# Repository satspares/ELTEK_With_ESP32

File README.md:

ELTEK Flatpack2 control using ESP32/c3 DWIN Display DMG48320C035_03WTC (480x320) or any DWIN TTL 800x480 display eg. DMG80480C043_01WTC.

18th September 2025 added config for DWIN Display DMG48270C043_04WTC 480x272 (change link on display to ttl).

Added Eltek network ID change to new menu item.

In the can-bus-kicad directory is a PCB design using ESP32c3 but you can use any ESP32 (5v supply needed) and a sn65hvd230 CAN Chip.

I am still working on the code for the older Flatpack2's so the code is not complete yet (fine for V3 Elteks)

The displays are from the DWIN Store on Aliexpress about 18.00usd plus carriage DMG48270C043_04WTC recommended.

As the Eltex was designed to charge batteries the current limit when active reduces the output voltage to approx. 47volts.
When this happens we display a warning and sound a beep also put a ESP32 output pin high. (pull a relay etc. with a driver transistor)

The folder to upload to the display via. sdcard is DWIN_SET
Its also worth looking at the DWIN docs. in my github https://github.com/satspares/DWIN_DGUS_HMI

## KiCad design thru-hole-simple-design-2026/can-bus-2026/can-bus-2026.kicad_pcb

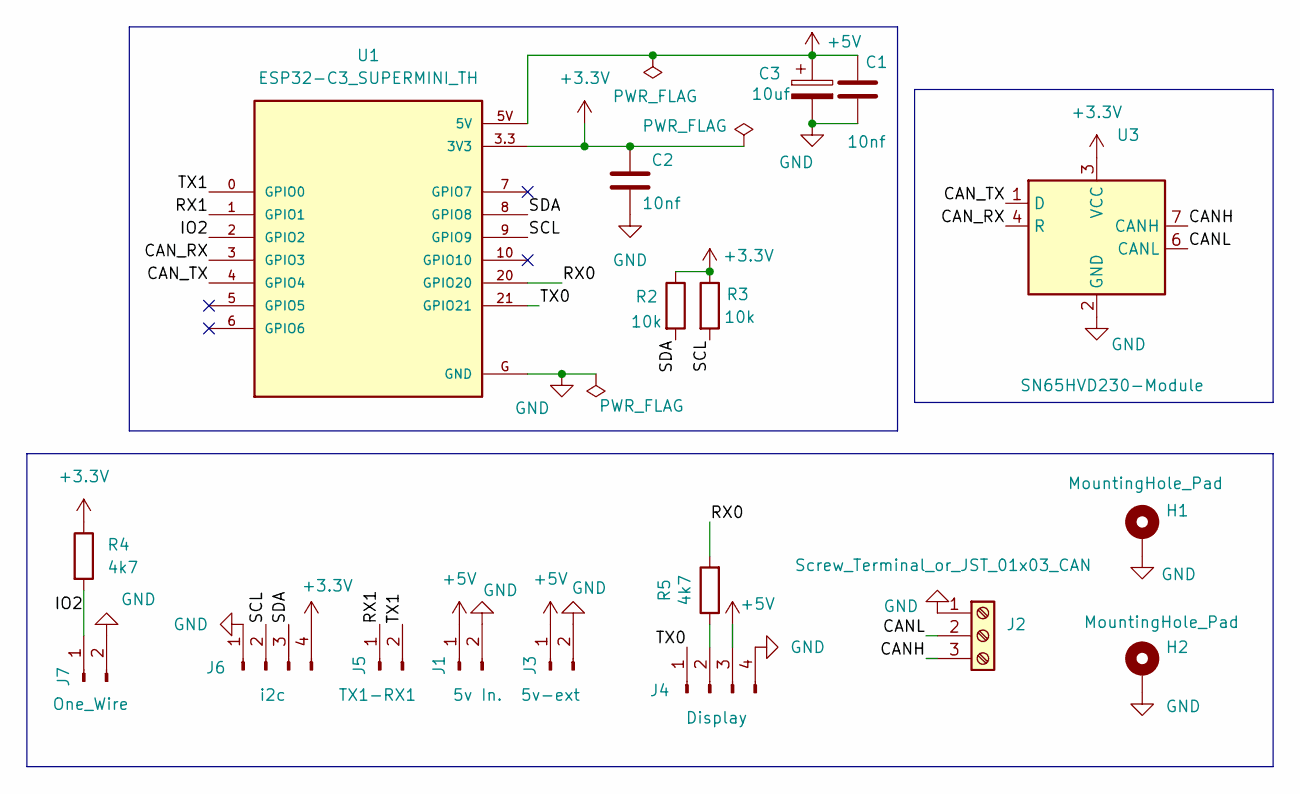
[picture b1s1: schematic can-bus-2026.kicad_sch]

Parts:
C1, C2: 10nf; C_Disc_D3.4mm_W2.1mm_P2.50mm
C3: 10uf; CP_Radial_D5.0mm_P2.50mm
H1, H2: MountingHole_Pad; MountingHole_3.5mm_Pad_Via
J1: 5v In.; JST_EH_B2B-EH-A_1x02_P2.50mm_Vertical
J2: Screw_Terminal_or_JST_01x03_CAN; TerminalBlock_Xinya_XY308-2.54-3P_1x03_P2.54mm_Horizontal
J3: 5v-ext; JST_EH_B2B-EH-A_1x02_P2.50mm_Vertical
J4: Display; JST_EH_B4B-EH-A_1x04_P2.50mm_Vertical
J5: TX1-RX1; JST_EH_B2B-EH-A_1x02_P2.50mm_Vertical
J6: i2c; JST_EH_B4B-EH-A_1x04_P2.50mm_Vertical
J7: One_Wire; JST_EH_B2B-EH-A_1x02_P2.50mm_Vertical
R2, R3: 10k; R_Axial_DIN0207_L6.3mm_D2.5mm_P7.62mm_Horizontal
R4, R5: 4k7; R_Axial_DIN0207_L6.3mm_D2.5mm_P7.62mm_Horizontal
U1: ESP32-C3_SUPERMINI_TH; MODULE_ESP32-C3_SUPERMINI
U3: SN65HVD230-Module

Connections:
+3.3V: C2.1, J6.4, R2.1, R3.1, R4.1, U1.3.3 (3V3), U3.3 (VCC)
+5V: C1.1, C3.1, J1.1, J3.1, J4.3, U1.5V
/CANH: J2.3, U3.7 (CANH)
/CANL: J2.2, U3.6 (CANL)
/CAN_RX: U1.3 (GPIO3), U3.4 (R)
/CAN_TX: U1.4 (GPIO4), U3.1 (D)
/IO2: J7.1, R4.2, U1.2 (GPIO2)
/RX0: R5.2, U1.20 (GPIO20)
/RX1: J5.1, U1.1 (GPIO1)
/SCL: J6.2, R3.2, U1.9 (GPIO9)
/SDA: J6.3, R2.2, U1.8 (GPIO8)
/TX0: J4.1, U1.21 (GPIO21)
/TX1: J5.2, U1.0 (GPIO0)
GND: C1.2, C2.2, C3.2, H1.1, H2.1, J1.2, J2.1, J3.2, J4.4, J6.1, J7.2, U1.G (GND), U3.2 (GND)
unnamed: J4.2, R5.1

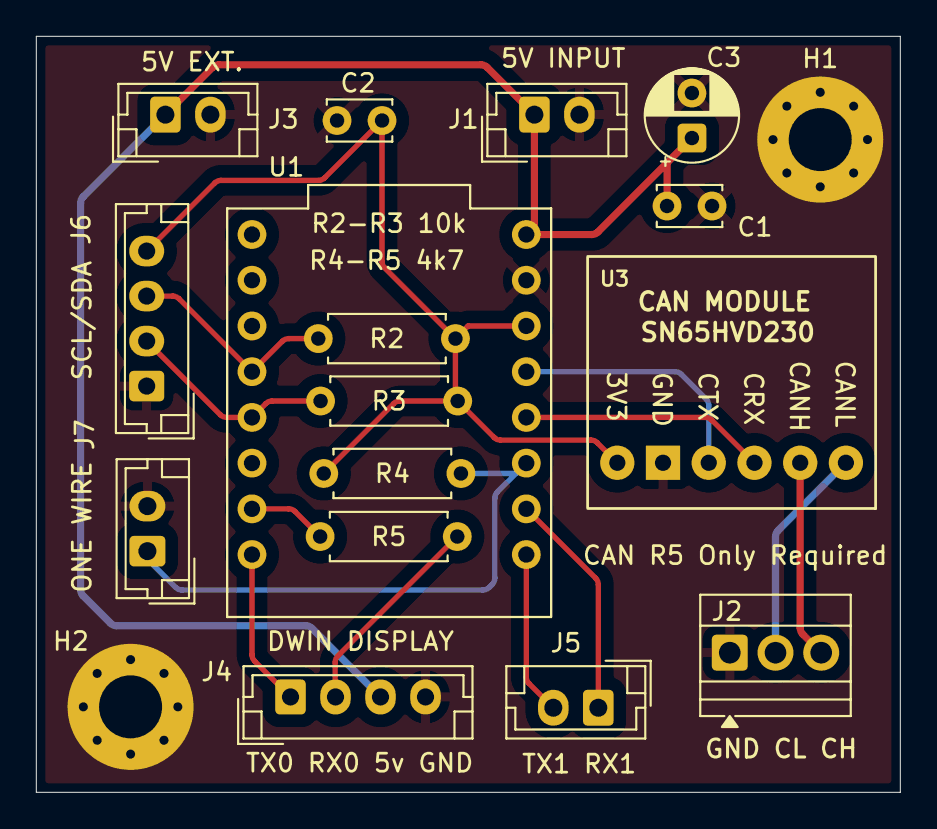
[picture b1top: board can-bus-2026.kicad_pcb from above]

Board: 2 copper layers, 48.0 x 42.0 mm, 18 parts (0 on the bottom side), 15 nets.

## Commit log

2025-05-21 First Upload 21-May-2025
2025-05-21 Update LICENSE
2025-05-21 Clean Up
2025-05-21 Add images
2025-05-21 Update Images
2025-05-21 upload display files.
2025-06-06 small change allow set session on startup option in includes.h
2025-08-08 Add 800x480 display code
2025-08-08 modified READ.md
2025-09-10 add expressif can self test
2025-09-13 add text only
2025-09-25 Add Eltek network ID change to displays
2026-04-02 clean up pcb add beep at startup
2026-04-02 clean up board
2026-04-10 Tidy up code fix possible bugs
2026-04-10 make some display buttons larger
2026-04-11 improve serial comms.- fix bugs - tidy code
2026-04-11 turn off display debug
2026-04-11 add windows platformio sample
2026-04-12 Improve Serial Comms.
2026-04-12 RELIABILITY FIXES.
2026-04-20 Add simple thru-hole-pcb-design
2026-05-03 update dwin display library
